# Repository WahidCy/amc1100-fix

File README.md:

# amc1100-fix
this is schematic and board design of AMC1100 with integrated differential to single ended signal that suites with 3.3V adc max voltage

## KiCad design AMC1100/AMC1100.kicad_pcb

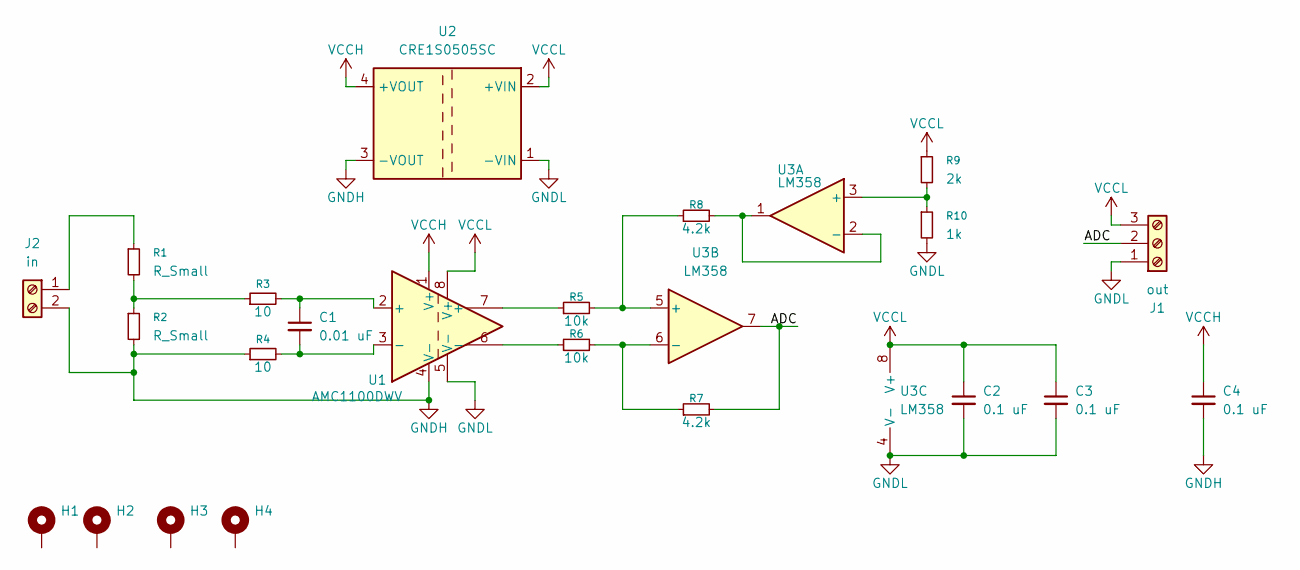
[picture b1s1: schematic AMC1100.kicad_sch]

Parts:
C1: 0.01 uF; C_Disc_D3.0mm_W1.6mm_P2.50mm
C2, C3, C4: 0.1 uF; C_Disc_D3.0mm_W1.6mm_P2.50mm
H1, H2, H3, H4: MountingHole_Pad; MountingHole_3.2mm_M3_Pad_Via
J1: out; Altech_AK100_1x03_P5.00mm
J2: in; Altech_AK100_1x02_P5.00mm
R1, R2: R_Small; R_Axial_DIN0207_L6.3mm_D2.5mm_P10.16mm_Horizontal
R3, R4: 10; R_Axial_DIN0207_L6.3mm_D2.5mm_P10.16mm_Horizontal
R5, R6: 10k; R_Axial_DIN0207_L6.3mm_D2.5mm_P10.16mm_Horizontal
R7, R8: 4.2k; R_Axial_DIN0207_L6.3mm_D2.5mm_P10.16mm_Horizontal
R9: 2k; R_Axial_DIN0207_L6.3mm_D2.5mm_P10.16mm_Horizontal
R10: 1k; R_Axial_DIN0207_L6.3mm_D2.5mm_P10.16mm_Horizontal
U1: AMC1100DWV; DIP-8_W7.62mm_Socket_LongPads
U2: CRE1S0505SC; Converter_DCDC_Murata_CRE1xxxxxxSC_THT
U3: LM358; DIP-8_W7.62mm_Socket_LongPads

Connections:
/ADC: J1.2, R7.2, U3.7
GNDH: C4.2, J2.2, R2.2, R4.1, U1.4 (V-), U2.3 (-VOUT)
GNDL: C2.2, C3.2, J1.1, R10.2, U1.5 (V-), U2.1 (-VIN), U3.4 (V-)
unnamed: C1.1, R3.2, U1.2 (+)
unnamed: C1.2, R4.2, U1.3 (-)
unnamed: J2.1, R1.1
unnamed: R1.2, R2.1, R3.1
unnamed: R5.1, U1.7 (+)
unnamed: R6.1, U1.6 (-)
unnamed: R9.2, R10.1, U3.3 (+)
unnamed: R8.2, U3.1, U3.2 (-)
unnamed: R5.2, R8.1, U3.5 (+)
unnamed: R6.2, R7.1, U3.6 (-)
VCCH: C4.1, U1.1 (V+), U2.4 (+VOUT)
VCCL: C2.1, C3.1, J1.3, R9.1, U1.8 (V+), U2.2 (+VIN), U3.8 (V+)

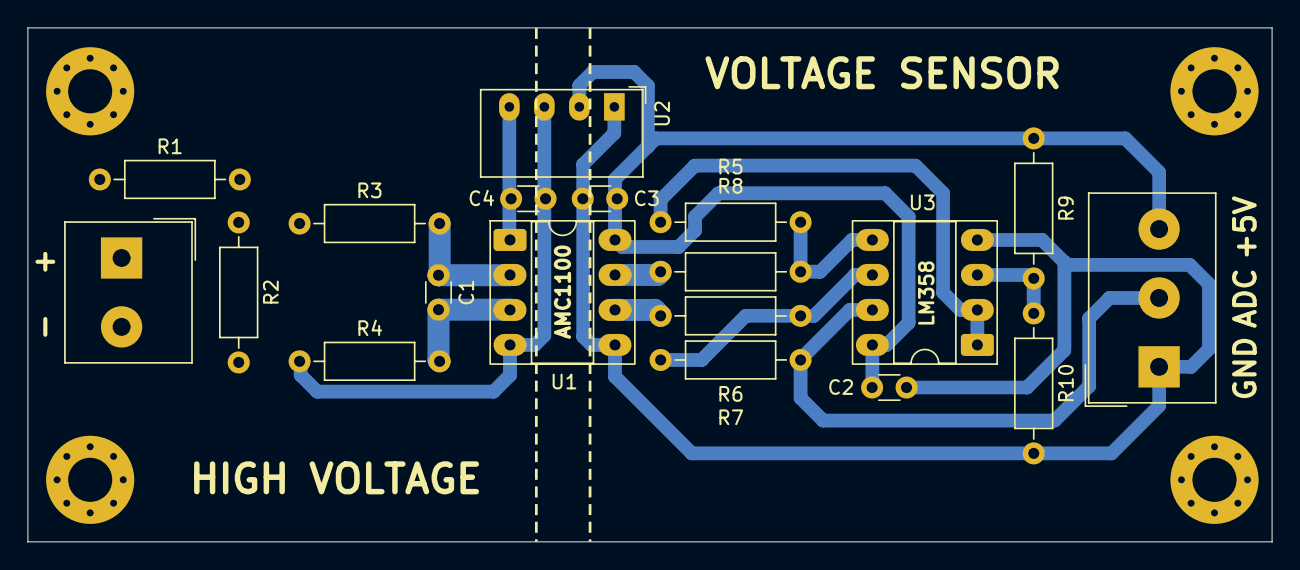
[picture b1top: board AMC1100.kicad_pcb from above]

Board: 2 copper layers, 90.3 x 37.3 mm, 23 parts (0 on the bottom side), 15 nets.

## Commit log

2025-04-15 Add files via upload
    first upload
